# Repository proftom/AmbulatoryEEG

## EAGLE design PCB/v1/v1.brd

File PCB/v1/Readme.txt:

For wed 28th manufacture 0.8mm train.

All holes plated through hole. 

If DRC are small and likely to cause no problem, please continue manfacture. Please use your best judgement. 
I manufactured this board at home a couple of weeks ago, with some even finer tracks, have made this easier, so should be fine for you guys. Only having it done professionally to improve RF, and make use of through hole technology.   
Please try to manufacture - need this by next week (wed 4th/thurs 5th june) :)

I also include the .brd file (EAGLE), if that helps

Please ring 07511117866 for any questions.

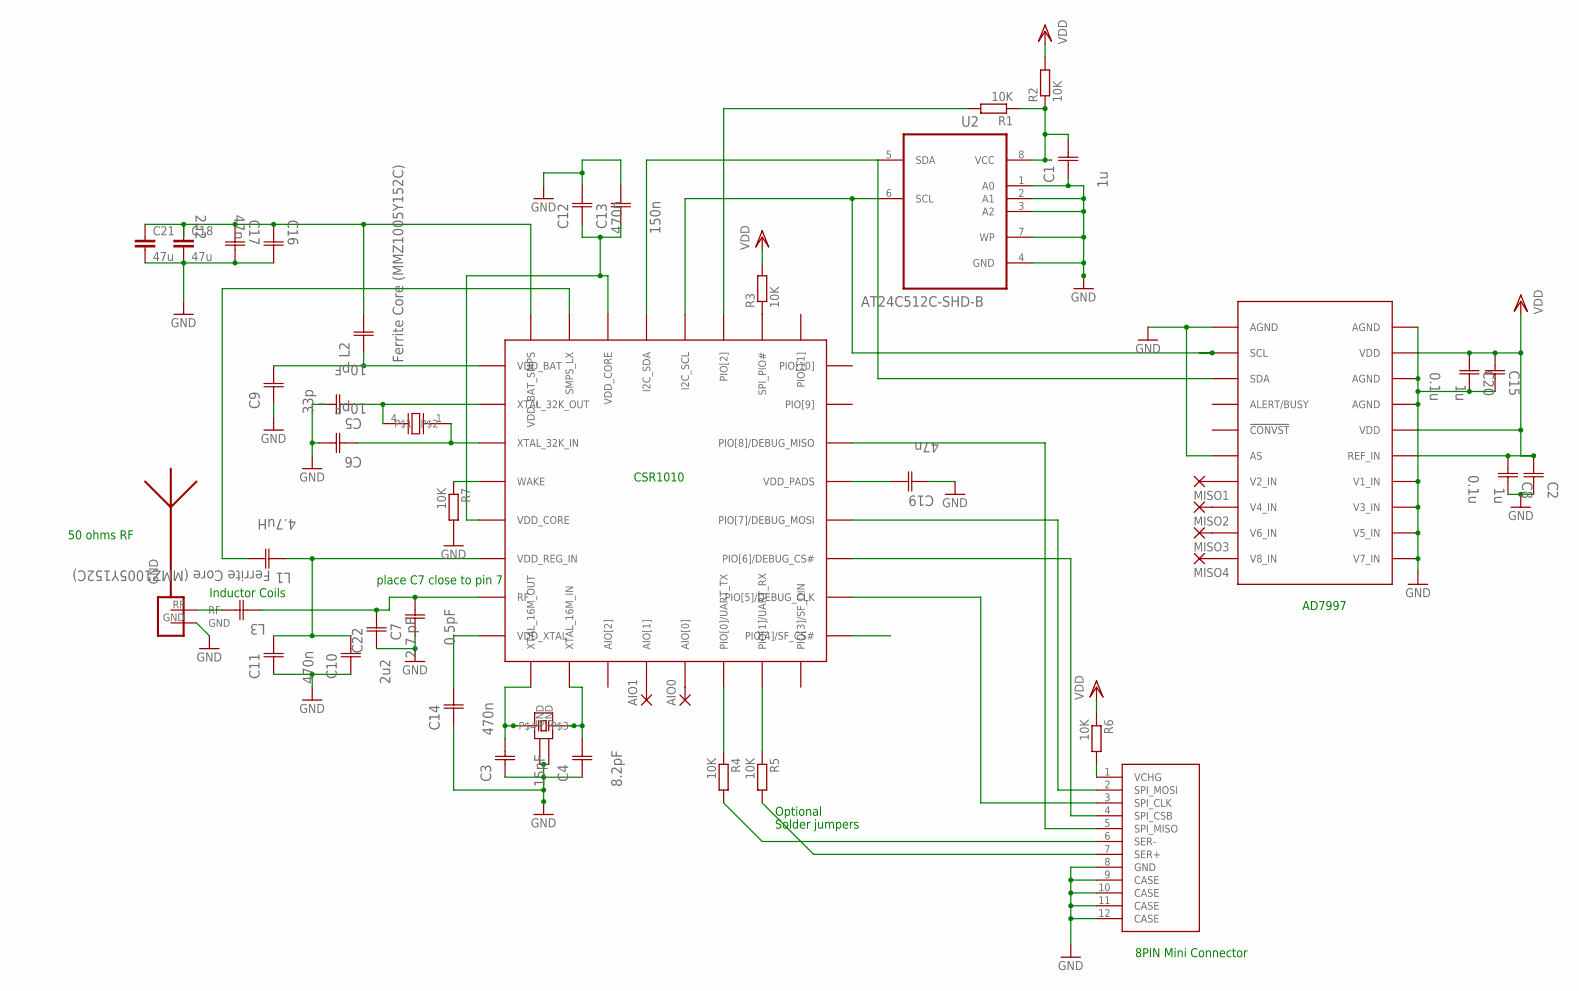
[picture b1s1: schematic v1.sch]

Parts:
AIO0, AIO1: 1,6/0,8
C1, C2, C15: 1u; CAPC1005X60N
C3: 15pF; CAPC1005X60N
C4: 8.2pF; CAPC1005X60N
C5, C6: 10pF; CAPC1005X60N
C7: 0.5pF; CAPC1005X60N
C8, C20: 0.1u; CAPC1005X60N
C9: 33p; CAPC1005X60N
C10, C17: 2u2; CAPC1005X60N
C11, C12, C14: 470n; CAPC1005X60N
C13: 150n; CAPC1005X60N
C16, C19: 47n; CAPC1005X60N
C18, C21: 47u; C0805
C22: 2.7 pF; CAPC1005X60N
GND: ANTENNA_1LEFT; SWRA117D_LEFT
L1: 4.7uH; CAPC3225X127N
L2, L3: Ferrite Core (MMZ1005Y152C); CAPC1005X60N
MISO1, MISO2, MISO3, MISO4: 1,6/0,8
R1, R2, R3, R4, R5, R6, R7: 10K; R0402
U2: AT24C512C-SHD-B; SOIC127P798X216-8N
U$1: CSR1010A05-IQQM-R
U$2: 8PIN_SMT_CONNECTOR
U$3: TSX3225
U$4: SSP-T7-F
U$5: AD7997

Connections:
GND: C1.2 (C1), C2.2 (C1), C3.2 (C1), C4.2 (C1), C6.1 (C2), C7.2 (C1), C8.2 (C1), C9.2 (C1), C10.2 (C1), C11.2 (C1), C12.1 (C2), C13.1 (C2), C14.2 (C1), C15.2 (C1), C16.1 (C2), C17.1 (C2), C18.2, C19.2 (C1), C20.2 (C1), C21.2, C22.2 (C1), R7.2, U2.1 (A0), U2.2 (A1), U2.3 (A2), U2.4 (GND), U2.7 (WP), U$2.8 (GND), U$2.9 (CASE), U$2.10 (CASE), U$2.11 (CASE), U$2.12 (CASE), U$3.2 (GND), U$3.4 (GND), U$5.P$01 (AGND), U$5.P$03 (AGND), U$5.P$04 (AGND), U$5.P$07 (V1_IN), U$5.P$08 (V3_IN), U$5.P$09 (V5_IN), U$5.P$010 (V7_IN), U$5.P$015 (AS), U$5.P$020 (AGND)
unnamed: R3.1, U$1.SPI_PIO#
unnamed: R1.2, U$1.PIO[2]
unnamed: C1.1 (C2), R1.1, R2.1, U2.8 (VCC)
unnamed: U$1.PIO[8]/DEBUG_MISO, U$2.5 (SPI_MISO)
unnamed: L1.2 (C2), U$1.SMPS_LX
unnamed: R4.2, U$2.6 (SER-)
unnamed: C5.2 (C1), U$1.XTAL_32K_OUT, U$4.4
unnamed: C6.2 (C1), U$1.XTAL_32K_IN, U$4.1
unnamed: AIO0.1, U$1.AIO[0]
unnamed: C3.1 (C2), U$1.XTAL_16M_OUT, U$3.1
unnamed: C4.1 (C2), U$1.XTAL_16M_IN, U$3.3
unnamed: U$1.PIO[6]/DEBUG_CS#, U$2.4 (SPI_CSB)
unnamed: C9.1 (C2), L2.2 (C1), U$1.VDD_BAT
unnamed: AIO1.1, U$1.AIO[1]
unnamed: C14.1 (C2), U$1.VDD_XTAL
unnamed: R5.2, U$2.7 (SER+)
unnamed: R4.1, U$1.PIO[0]/UART_TX
unnamed: R5.1, U$1.PIO[1]/UART_RX
unnamed: C10.1 (C2), C11.1 (C2), L1.1 (C1), U$1.VDD_REG_IN
unnamed: R6.2, U$2.1 (VCHG)
unnamed: C7.1 (C2), C22.1 (C2), L3.2 (C1), U$1.RF
unnamed: MISO1.1, U$5.P$014 (V2_IN)
unnamed: R7.1, U$1.WAKE
unnamed: U$1.PIO[7]/DEBUG_MOSI, U$2.2 (SPI_MOSI)
unnamed: U$1.PIO[5]/DEBUG_CLK, U$2.3 (SPI_CLK)
unnamed: MISO3.1, U$5.P$012 (V6_IN)
unnamed: MISO2.1, U$5.P$013 (V4_IN)
unnamed: MISO4.1, U$5.P$011 (V8_IN)
unnamed: C19.1 (C2), U$1.VDD_PADS
unnamed: U2.5 (SDA), U$1.I2C_SDA, U$5.P$018 (SDA)
unnamed: C16.2 (C1), C17.2 (C1), C18.1, C21.1, L2.1 (C2), U$1.VDD_BAT_SMPS
SCL: U2.6 (SCL), U$1.I2C_SCL, U$5.P$019 (SCL)
VDD: C2.1 (C2), C8.1 (C2), C15.1 (C2), C20.1 (C2), R2.2, R3.2, R6.1, U$5.P$02 (VDD), U$5.P$05 (VDD), U$5.P$06 (REF_IN)
VDD_CORE: C12.2 (C1), C13.2 (C1), U$1.VDD_CORE, U$1.VDD_CORE@1 (VDD_CORE)

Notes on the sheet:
Optional
Solder jumpers
50 ohms RF
Inductor Coils
place C7 close to pin 7
CSR1010
AD7997
8PIN Mini Connector

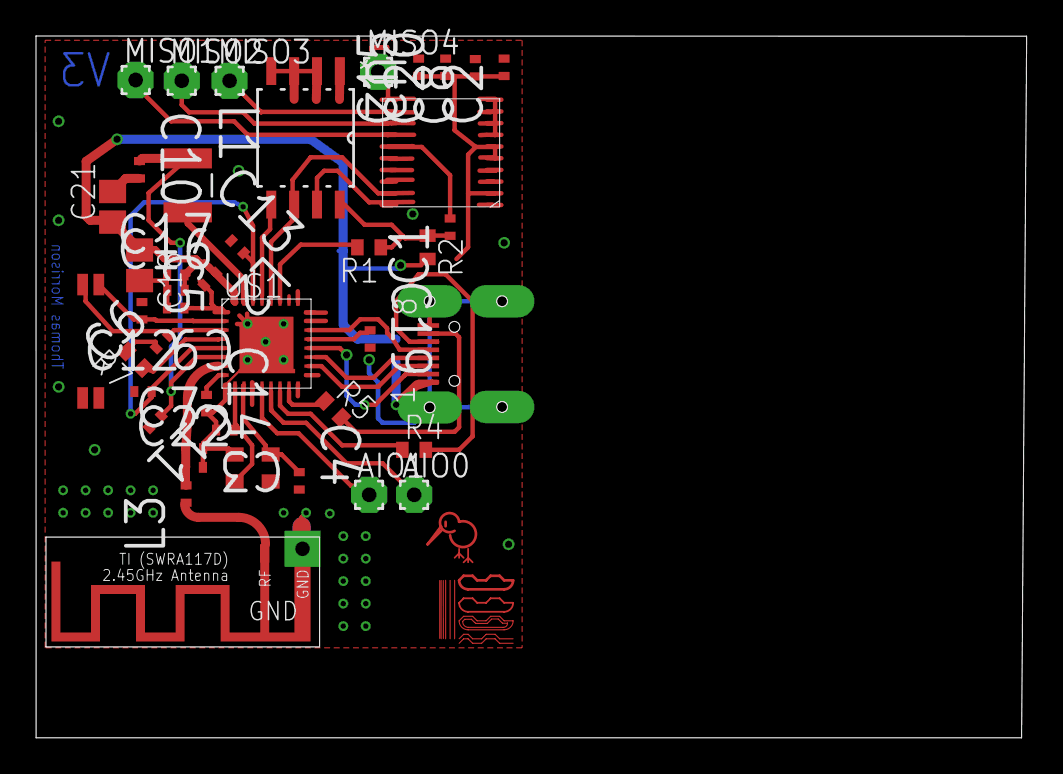
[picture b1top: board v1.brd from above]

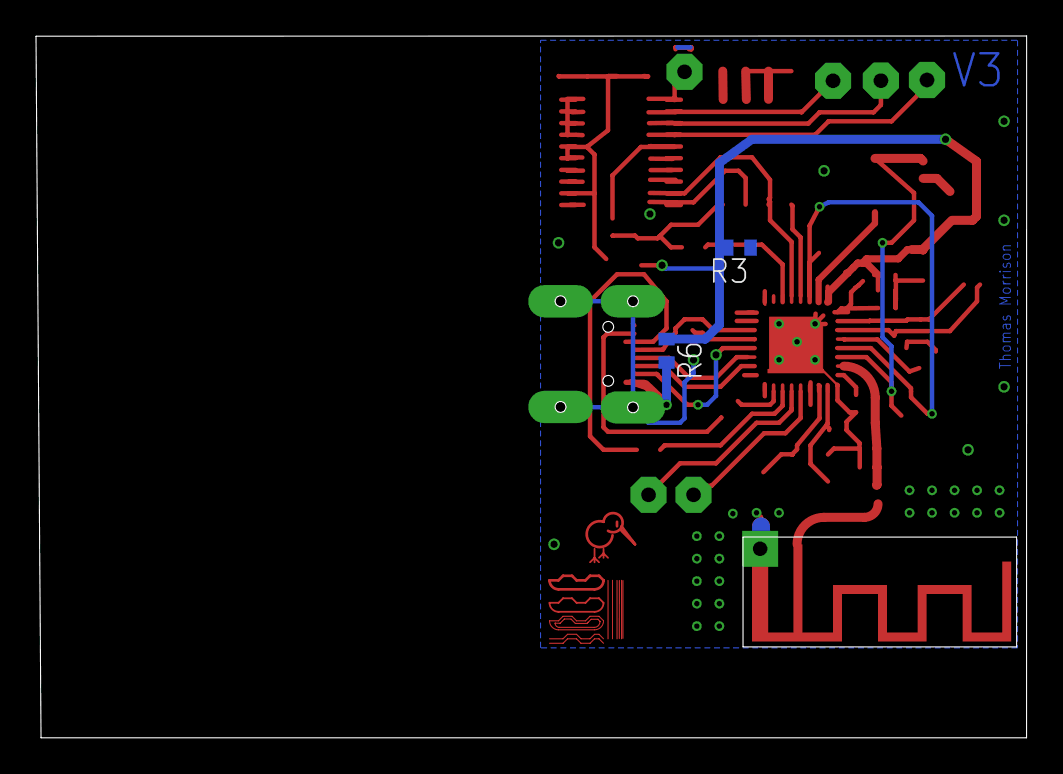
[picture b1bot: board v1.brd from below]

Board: 2 copper layers, 55.0 x 39.0 mm, 45 parts (2 on the bottom side), 35 nets.

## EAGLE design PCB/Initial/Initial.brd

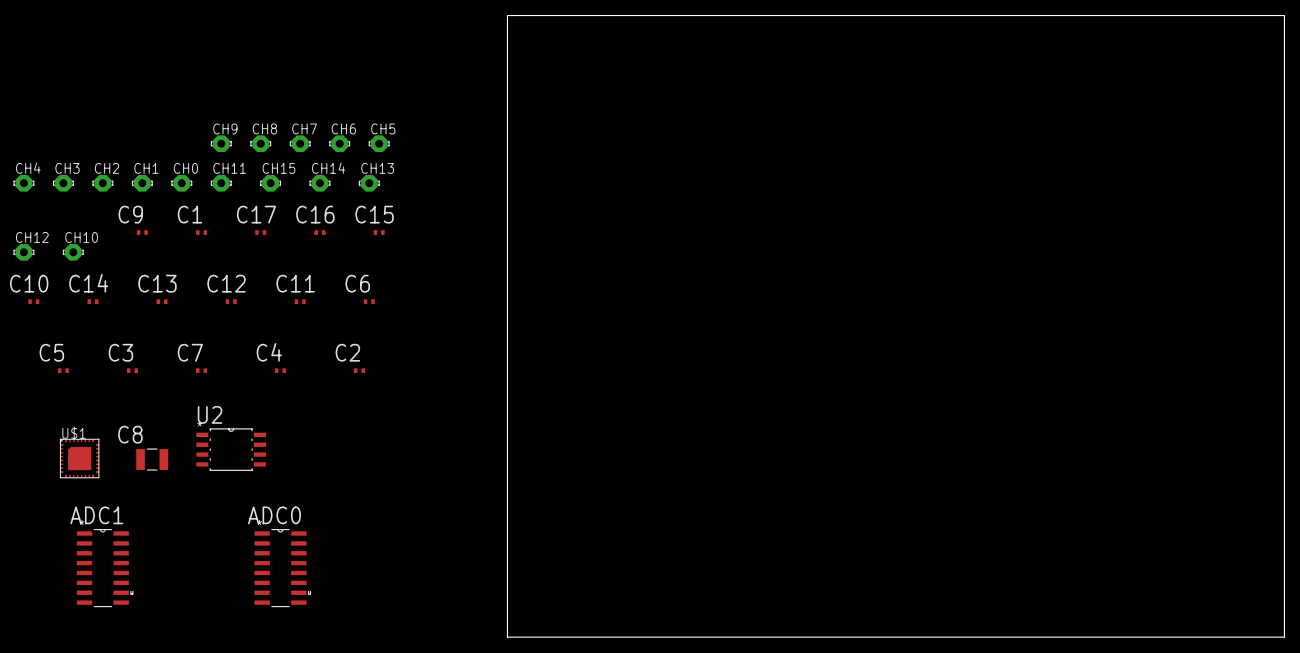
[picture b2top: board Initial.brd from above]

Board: 2 copper layers, 100.0 x 80.0 mm, 37 parts (0 on the bottom side), 34 nets, no tracks yet.

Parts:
ADC0, ADC1: MCP3008-I/SL; SOIC127P600X175-16N
C1: 47u; CAPC1005X60N
C2: 4.7uH; CAPC1005X60N
C3: 15pF; CAPC1005X60N
C4: 8.2pF; CAPC1005X60N
C5, C6: 10pF; CAPC1005X60N
C7: 0.5pF; CAPC1005X60N
C8: 4.7uH; CAPC3225X170N
C9: 33p; CAPC1005X60N
C10, C17: 4u7; CAPC1005X60N
C11, C12, C14: 470n; CAPC1005X60N
C13: 150n; CAPC1005X60N
C15, C16: 47n; CAPC1005X60N
CH0, CH1, CH2, CH3, CH4, CH5, CH6, CH7, CH8, CH9, CH10, CH11, CH12, CH13, CH14, CH15: LSP10
U2: AT24C512C-SHD-B; SOIC127P798X216-8N
U$1: CSR1010A05-IQQM-R

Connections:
GND: ADC0.9, ADC0.14, ADC1.9, ADC1.14, C1.2, C3.2, C4.2, C5.1, C6.1, C7.1, C7.2, C9.2, C10.2, C11.2, C12.1, C13.1, C14.2, C15.1, C16.1, C17.1, U2.1, U2.2, U2.3, U2.4, U2.7, U$1.RF, U$1.WAKE
unnamed: ADC0.8, CH7.MP
unnamed: ADC0.7, CH6.MP
unnamed: ADC0.6, CH5.MP
unnamed: ADC0.5, CH4.MP
unnamed: ADC0.4, CH3.MP
unnamed: ADC0.3, CH2.MP
unnamed: ADC0.2, CH1.MP
unnamed: ADC0.1, CH0.MP
unnamed: ADC1.8, CH15.MP
unnamed: ADC1.7, CH14.MP
unnamed: ADC1.6, CH13.MP
unnamed: ADC1.5, CH12.MP
unnamed: ADC1.4, CH11.MP
unnamed: ADC1.3, CH10.MP
unnamed: ADC1.2, CH9.MP
unnamed: ADC1.1, CH8.MP
unnamed: U2.5, U$1.I2C_SDA
unnamed: U2.6, U$1.I2C_SCL
unnamed: C8.1, U$1.SMPS_LX
unnamed: ADC0.13, ADC1.13, U$1.PIO[5]/DEBUG_CLK
unnamed: ADC0.12, ADC1.12, U$1.PIO[8]/DEBUG_MISO
unnamed: ADC0.11, ADC1.11, U$1.PIO[7]/DEBUG_MOSI
unnamed: ADC1.10, U$1.PIO[9]
unnamed: ADC0.10, U$1.PIO[4]/SF_CS#
unnamed: C5.2, U$1.XTAL_32K_OUT
unnamed: C6.2, U$1.XTAL_32K_IN
unnamed: C12.2, C13.2, U$1.VDD_CORE, U$1.VDD_CORE@1
unnamed: C3.1, U$1.XTAL_16M_OUT
unnamed: C2.2, C9.1, U$1.VDD_BAT
unnamed: C8.2, C10.1, C11.1, U$1.VDD_REG_IN
unnamed: C1.1, C2.1, C15.2, C16.2, C17.2, U$1.VDD_BAT_SMPS, U$1.VDD_PADS
unnamed: C14.1, U$1.VDD_XTAL
VDD: ADC0.15, ADC0.16, ADC1.15, ADC1.16, U2.8

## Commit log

2014-03-01 Initial circuit design commit
2014-03-01 before pad naming
2014-03-01 before pad naming (correct orientation)
2014-03-01 naming done, minus the corner pads (seem polygons cannot be converted to pads
2014-03-01 added symbol with names. Removing angular pads before making device
2014-03-01 symbol and package done
2014-03-02 Need to draw Xtals, SPI_mini_interface, and probably some more. Might update center of CSR1010A05 with a ground pad. Need to double check SPI compatibility (might be overlayed with I2C)
2014-03-02 need to add xtal footprints, solder bridge components and correct mini 8pin SPI connector
2014-03-02 xstals done. Connecot and battery need stamping
2014-03-02 Need datasheet for 8 pin connector
2014-03-02 need to do some bloody exercise. added list of TODOs on schem
2014-03-06 more libs
2014-03-06 connector done. final modifications to schematic
2014-03-07 using project to link schem and board. Need RF still
2014-03-07 need to do the RF and track up
2014-03-07 corrected battery, still need RF. laying out zzzz
2014-03-08 push to work from main pc
2014-03-08 takes its time
2014-03-10 commit before school
2014-03-12 getting there
2014-03-13 just needs an RF antenna
2014-03-13 just needs an RF F-antenna
2014-03-16 quickly added antenna
2014-03-17 trying to make antenna board edge
2014-03-26 latest
2014-03-26 expose pads more and add other ADC
2014-03-28 added new chip, brought out solder mask. Need to check crystal pads and ground connections
2014-03-28 now with library
2014-03-28 need to check over
2014-03-28 do a once over, then fab
2014-05-10 before watanya layout
2014-05-10 ripped up. need to correct ADC package
2014-05-10 watanya about to start...
2014-05-11 watanya design. needs tweaking. RF. Want to pull components in tighter
2014-05-11 toms here
2014-05-11 making more like manufacturing kit
2014-05-12 final check and submit
2014-05-12 board submitted (albeit without tstop over QFN pad
2014-05-14 time to populate the board
2014-05-19 begin work on final board
2014-05-26 writing software
2014-05-26 time for master merge
2014-05-26 added credit
2014-05-26 tried adding timeout timer
2014-05-26 setting meas and CI to 10ms, after first 3 CI, seems stable
2014-05-27 added ADC and battery holder to schem
2014-05-27 added new ADC along with contact points
2014-05-27 need to remove drill holes and go through checklist
2014-05-27 removed connector drill holes
2014-05-27 final checked + silk screen
2014-05-27 submitting for fabrication
2014-05-28 PCB done and sent off. Fab confirms in production
2014-05-28 now write different value to slave
2014-05-28 let's turn it into EEG
2014-05-28 modified UUID_HEART_RATE_SERVICE
2014-05-28 attempt to change HR GATT DB to EEG functionality
2014-05-28 names changed, still using HR UUIDs
2014-05-28 removed some redudant HR defines
2014-05-28 changed sensor name
2014-05-28 modified names, added property definition to EEG_ACQUISITION_RATE in GATT DB, but no implementation
2014-05-28 appearance changes to unknonw in GAP service, UUIDs still HR
2014-05-28 does seem to like HeartRate under the surface - could keep it like this. Attempting to modify now, otherwise this will act as fallback
2014-05-28 done it manual way, but stops working after a few seconds. Maybe event handler destroyed on button exit?
2014-05-28 the event handler is being destroyed on button exit, need to move object lifetime into proper management enviroment. Tested using while(true)
2014-05-28 bedtime
2014-05-29 changing UUIDs
2014-05-29 modify file names
2014-05-29 renaming header files
2014-05-29 one more header files and some db files todo
2014-05-29 all files renamed
2014-05-29 first app commit
2014-05-29 working on sending channel map
2014-05-29 endianess is back to front at the byte granularity
2014-05-29 corrected endianess along with ability to write to channel map and acquisition rate
2014-05-30 batching graph update
2014-05-30 testing sparrow chart
2014-05-31 channel map update for 1 channel
2014-05-31 channel map char done
2014-05-31 awaiting packet packing impl
2014-05-31 report first commit
2014-06-01 battery char code looks correct, finds device, but fails to find service from device id - strange
2014-06-01 report packages added, began acknowledgement and abstract
2014-06-01 re-writing intro/abstract, converting from original interim word format and starting off new sections
2014-06-01 Adding to theory
2014-06-01 Intro to theory improved
2014-06-02 bed time
2014-06-02 still wiriting theory
2014-06-02 writing up nrf8001
2014-06-02 explaining pairing process, interval. will introduce CIs, and derivation of maximum throughput next
2014-06-02 filled theoretical maximum calcs in
2014-06-03 radio eval
2014-06-03 writing up CSR1010
2014-06-03 added nrf8001 cap
2014-06-03 order components
2014-06-04 trying to get sync charts up and running
2014-06-04 harbour
2014-06-05 board manufacture at school
2014-06-06 more on NAND, ADC and adding engineering discussion into CSR1010
2014-06-06 added references
2014-06-06 social
2014-06-07 writing final component choice
2014-06-07 added schem
2014-06-07 prelim research OK
2014-06-07 need to do first few sections
2014-06-08 motiviation
2014-06-08 want a chocolate bar
2014-06-11 power analysis
2014-06-12 power analysis and thruoghput
2014-06-12 power & throughput analysis
2014-06-12 continue monday
2014-06-15 attempting to finish throughput
2014-06-16 still writing throughput
2014-06-16 that'll do for throughput
2014-06-16 writing implemtation
2014-06-17 still writing implemtation
2014-06-17 still writing implemtation. Added application screen shot
2014-06-18 need to write eeg background then conclusion
2014-06-18 added assets
2014-06-18 back to big pc
2014-06-18 conclusion almost done. need to do power analysis
2014-06-19 i2c stuff added. need to finish power section and then add to conclusion then send for review
2014-06-20 going to pick up battery connectors. Reading report all through and correcting
2014-06-20 correcting spelling and stubs
2014-06-21 just need to do energy per bit and conclusion, then tidy up
2014-06-21 hurry up and finisht thomas
2014-06-21 i2c done
2014-06-21 come on come on
2014-06-21 conc and power anlaysis done. Homerun
2014-06-21 conc and power anlaysis done. Homerun2
2014-06-21 specification
2014-06-21 added pictures to uguide. Just need to do BOM
2014-06-21 submitted
2014-06-23 going to print at school
2014-06-24 need to make safe type converter
2014-06-24 converter done
2014-06-24 need to fix graphs
